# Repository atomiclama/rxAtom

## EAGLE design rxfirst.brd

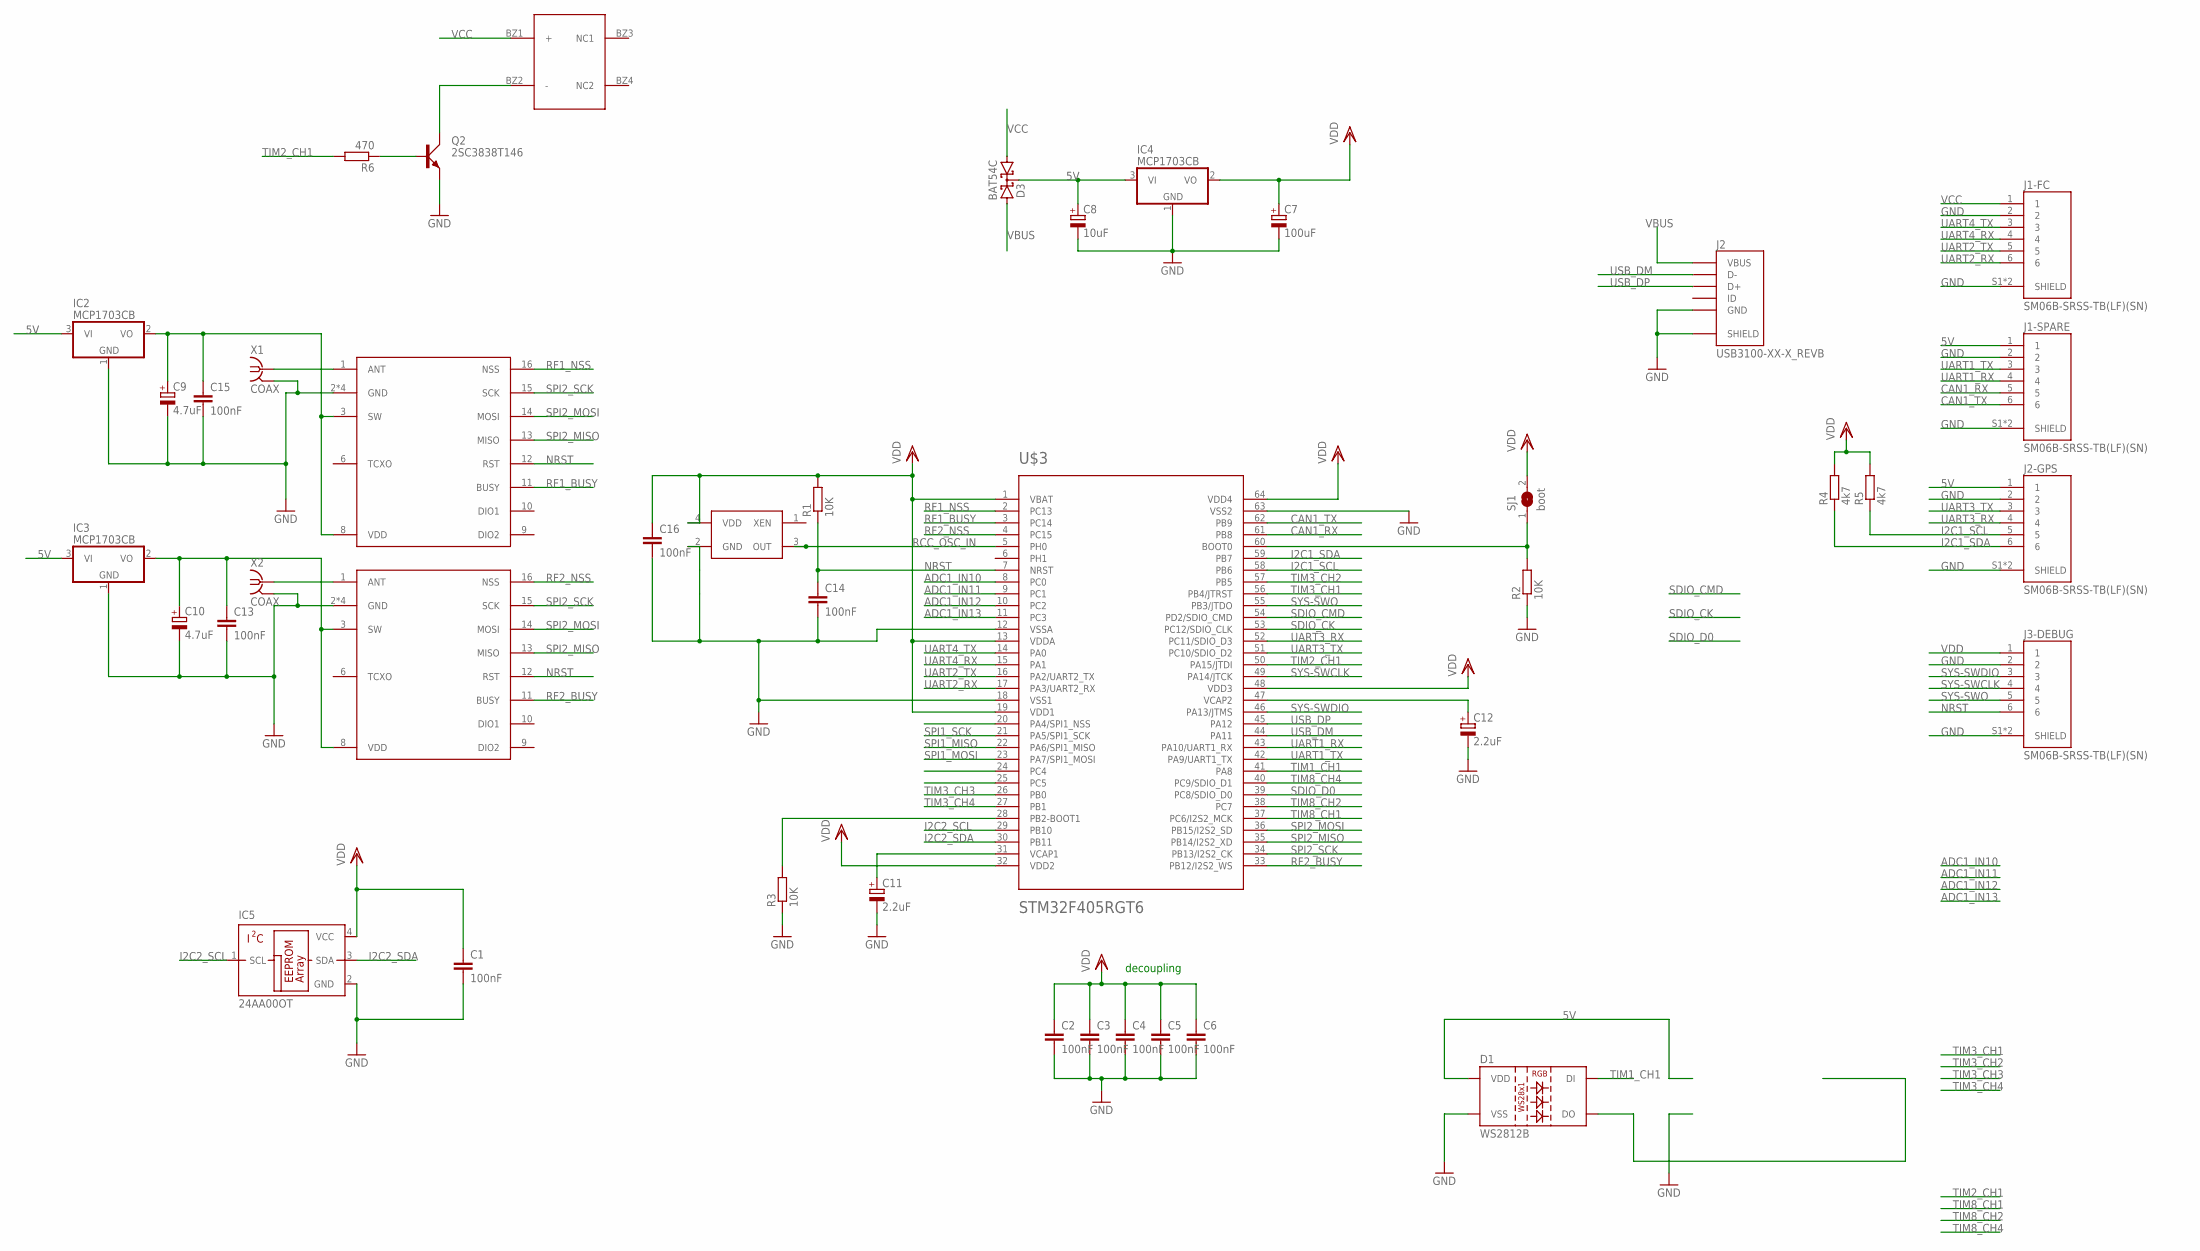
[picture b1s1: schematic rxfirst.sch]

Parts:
C1, C2, C3, C4, C5, C6, C13, C14, C15, C16: 100nF; C0603
C7: 100uF; SMC_A
C8: 10uF; SMC_A
C9, C10: 4.7uF; SMC_A
C11, C12: 2.2uF; SMC_A
D1: WS2812B
D3: BAT54C; SOT23
IC2, IC3, IC4: MCP1703CB; SOT23
IC5: 24AA00OT; SOT23-5L
J1-FC, J1-SPARE, J2-GPS, J3-DEBUG: SM06B-SRSS-TB(LF)(SN); JST_SM06B-SRSS-TB(LF)(SN)
J2: USB3100-XX-X_REVB; GCT_USB3100-XX-X_REVB
Q2: 2SC3838T146; SC59
R1, R2, R3: 10K; R0603
R4, R5: 4k7; R0603
R6: 470; R0603
RF1, RF2: DRF1262T; SMD
SJ1: boot; SJ
U$1: BZ; SND
U$3: STM32F405RGT6; TQFP64
U$4: XO; SMD
X1, X2: COAX; MMCX-J-P-X-ST-EM1-MKT

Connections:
5V: C8.+, D1.1 (VDD), D3.3 (CC), IC2.3 (VI), IC3.3 (VI), IC4.3 (VI), J1-SPARE.1, J2-GPS.1
ADC1_IN10: U$3.8 (PC0)
ADC1_IN11: U$3.9 (PC1)
ADC1_IN12: U$3.10 (PC2)
ADC1_IN13: U$3.11 (PC3)
CAN1_RX: J1-SPARE.5, U$3.61 (PB8)
CAN1_TX: J1-SPARE.6, U$3.62 (PB9)
GND: C1.2, C2.2, C3.2, C4.2, C5.2, C6.2, C7.-, C8.-, C9.-, C10.-, C11.-, C12.-, C13.2, C14.2, C15.2, C16.2, D1.3 (VSS), IC2.1 (GND), IC3.1 (GND), IC4.1 (GND), IC5.2 (GND), J1-FC.2, J1-FC.S1 (SHIELD), J1-FC.S2 (SHIELD), J1-SPARE.2, J1-SPARE.S1 (SHIELD), J1-SPARE.S2 (SHIELD), J2.5 (GND), J2.6 (SHIELD), J2.7 (SHIELD), J2.8 (SHIELD), J2.9 (SHIELD), J2-GPS.2, J2-GPS.S1 (SHIELD), J2-GPS.S2 (SHIELD), J3-DEBUG.2, J3-DEBUG.S1 (SHIELD), J3-DEBUG.S2 (SHIELD), Q2.E, R2.1, R3.1, RF1.2 (GND), RF1.4 (GND), RF1.5 (GND), RF1.7 (GND), RF2.2 (GND), RF2.4 (GND), RF2.5 (GND), RF2.7 (GND), U$3.12 (VSSA), U$3.18 (VSS1), U$3.63 (VSS2), U$4.2 (GND), X1.2@1 (GND), X1.2@2 (GND), X1.2@3 (GND), X1.2@4 (GND), X2.2@1 (GND), X2.2@2 (GND), X2.2@3 (GND), X2.2@4 (GND)
I2C1_SCL: J2-GPS.5, R5.1, U$3.58 (PB6)
I2C1_SDA: J2-GPS.6, R4.1, U$3.59 (PB7)
I2C2_SCL: IC5.1 (SCL), U$3.29 (PB10)
I2C2_SDA: IC5.3 (SDA), U$3.30 (PB11)
unnamed: RF1.1 (ANT), X1.1
unnamed: R3.2, U$3.28 (PB2-BOOT1)
unnamed: RF2.1 (ANT), X2.1
unnamed: C12.+, U$3.47 (VCAP2)
unnamed: C9.+, C15.1, IC2.2 (VO), RF1.3 (SW), RF1.8 (VDD)
unnamed: C10.+, C13.1, IC3.2 (VO), RF2.3 (SW), RF2.8 (VDD)
unnamed: Q2.B, R6.1
unnamed: Q2.C, U$1.BZ2 (-)
unnamed: C11.+, U$3.31 (VCAP1)
unnamed: R2.2, SJ1.1, U$3.60 (BOOT0)
NRST: C14.1, J3-DEBUG.6, R1.1, RF1.12 (RST), RF2.12 (RST), U$3.7 (NRST)
RCC_OSC_IN: U$3.5 (PH0), U$4.3 (OUT)
RF1_BUSY: RF1.11 (BUSY), U$3.3 (PC14)
RF1_NSS: RF1.16 (NSS), U$3.2 (PC13)
RF2_BUSY: RF2.11 (BUSY), U$3.33 (PB12/I2S2_WS)
RF2_NSS: RF2.16 (NSS), U$3.4 (PC15)
SDIO_CK: U$3.53 (PC12/SDIO_CLK)
SDIO_CMD: U$3.54 (PD2/SDIO_CMD)
SDIO_D0: U$3.39 (PC8/SDIO_D0)
SPI1_MISO: U$3.22 (PA6/SPI1_MISO)
SPI1_MOSI: U$3.23 (PA7/SPI1_MOSI)
SPI1_SCK: U$3.21 (PA5/SPI1_SCK)
SPI2_MISO: RF1.13 (MISO), RF2.13 (MISO), U$3.35 (PB14/I2S2_XD)
SPI2_MOSI: RF1.14 (MOSI), RF2.14 (MOSI), U$3.36 (PB15/I2S2_SD)
SPI2_SCK: RF1.15 (SCK), RF2.15 (SCK), U$3.34 (PB13/I2S2_CK)
SYS-SWCLK: J3-DEBUG.4, U$3.49 (PA14/JTCK)
SYS-SWDIO: J3-DEBUG.3, U$3.46 (PA13/JTMS)
SYS-SWO: J3-DEBUG.5, U$3.55 (PB3/JTDO)
TIM1_CH1: D1.4 (DI), U$3.41 (PA8)
TIM2_CH1: R6.2, U$3.50 (PA15/JTDI)
TIM3_CH1: U$3.56 (PB4/JTRST)
TIM3_CH2: U$3.57 (PB5)
TIM3_CH3: U$3.26 (PB0)
TIM3_CH4: U$3.27 (PB1)
TIM8_CH1: U$3.37 (PC6/I2S2_MCK)
TIM8_CH2: U$3.38 (PC7)
TIM8_CH4: U$3.40 (PC9/SDIO_D1)
UART1_RX: J1-SPARE.4, U$3.43 (PA10/UART1_RX)
UART1_TX: J1-SPARE.3, U$3.42 (PA9/UART1_TX)
UART2_RX: J1-FC.6, U$3.17 (PA3/UART2_RX)
UART2_TX: J1-FC.5, U$3.16 (PA2/UART2_TX)
UART3_RX: J2-GPS.4, U$3.52 (PC11/SDIO_D3)
UART3_TX: J2-GPS.3, U$3.51 (PC10/SDIO_D2)
UART4_RX: J1-FC.4, U$3.15 (PA1)
UART4_TX: J1-FC.3, U$3.14 (PA0)
USB_DM: J2.2 (D-), U$3.44 (PA11)
USB_DP: J2.3 (D+), U$3.45 (PA12)
VBUS: D3.2 (A2), J2.1 (VBUS)
VCC: D3.1 (A1), J1-FC.1, U$1.BZ1 (+)
VDD: C1.1, C2.1, C3.1, C4.1, C5.1, C6.1, C7.+, C16.1, IC4.2 (VO), IC5.4 (VCC), J3-DEBUG.1, R1.2, R4.2, R5.2, SJ1.2, U$3.1 (VBAT), U$3.13 (VDDA), U$3.19 (VDD1), U$3.32 (VDD2), U$3.48 (VDD3), U$3.64 (VDD4), U$4.4 (VDD)

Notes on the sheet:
decoupling

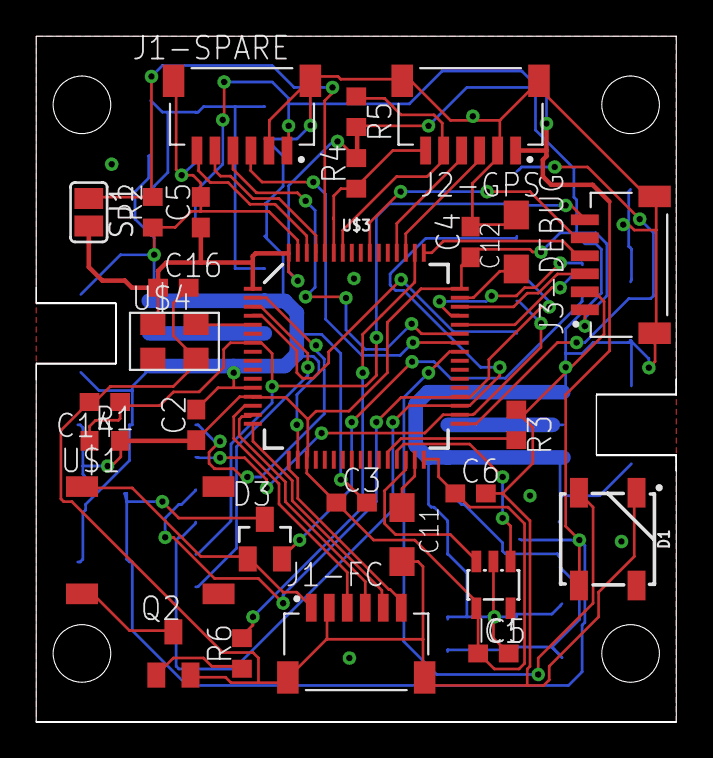
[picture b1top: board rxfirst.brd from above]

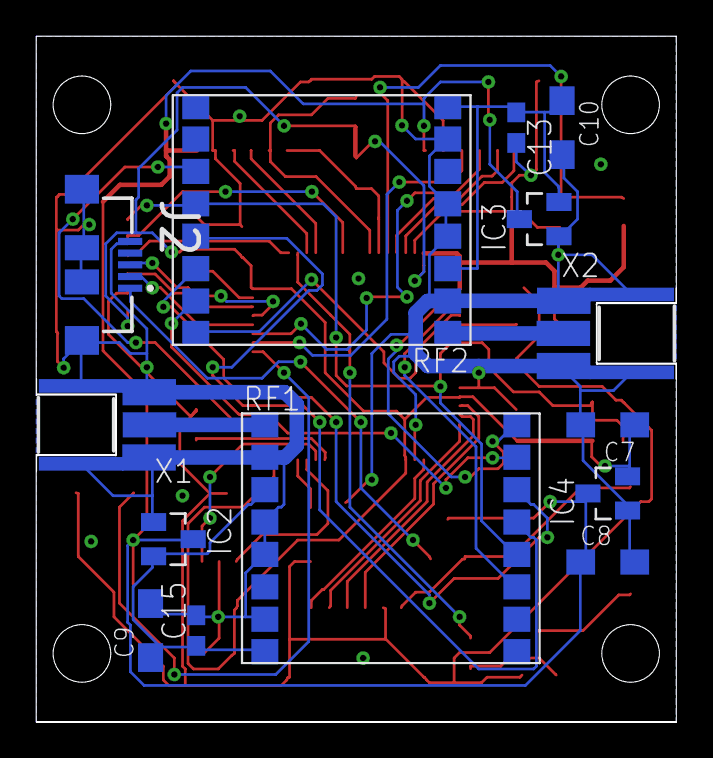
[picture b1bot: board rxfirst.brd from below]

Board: 2 copper layers, 35.6 x 38.1 mm, 42 parts (14 on the bottom side), 45 nets.

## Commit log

2019-11-25 first version manufactured.
2019-11-25 interim changes

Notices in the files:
parts and their libraries:
SparkFun-IC-Microcontroller: Licensing: Creative Commons ShareAlike 4.0 International - https://creativecommons.org/licenses/by-sa/4.0
